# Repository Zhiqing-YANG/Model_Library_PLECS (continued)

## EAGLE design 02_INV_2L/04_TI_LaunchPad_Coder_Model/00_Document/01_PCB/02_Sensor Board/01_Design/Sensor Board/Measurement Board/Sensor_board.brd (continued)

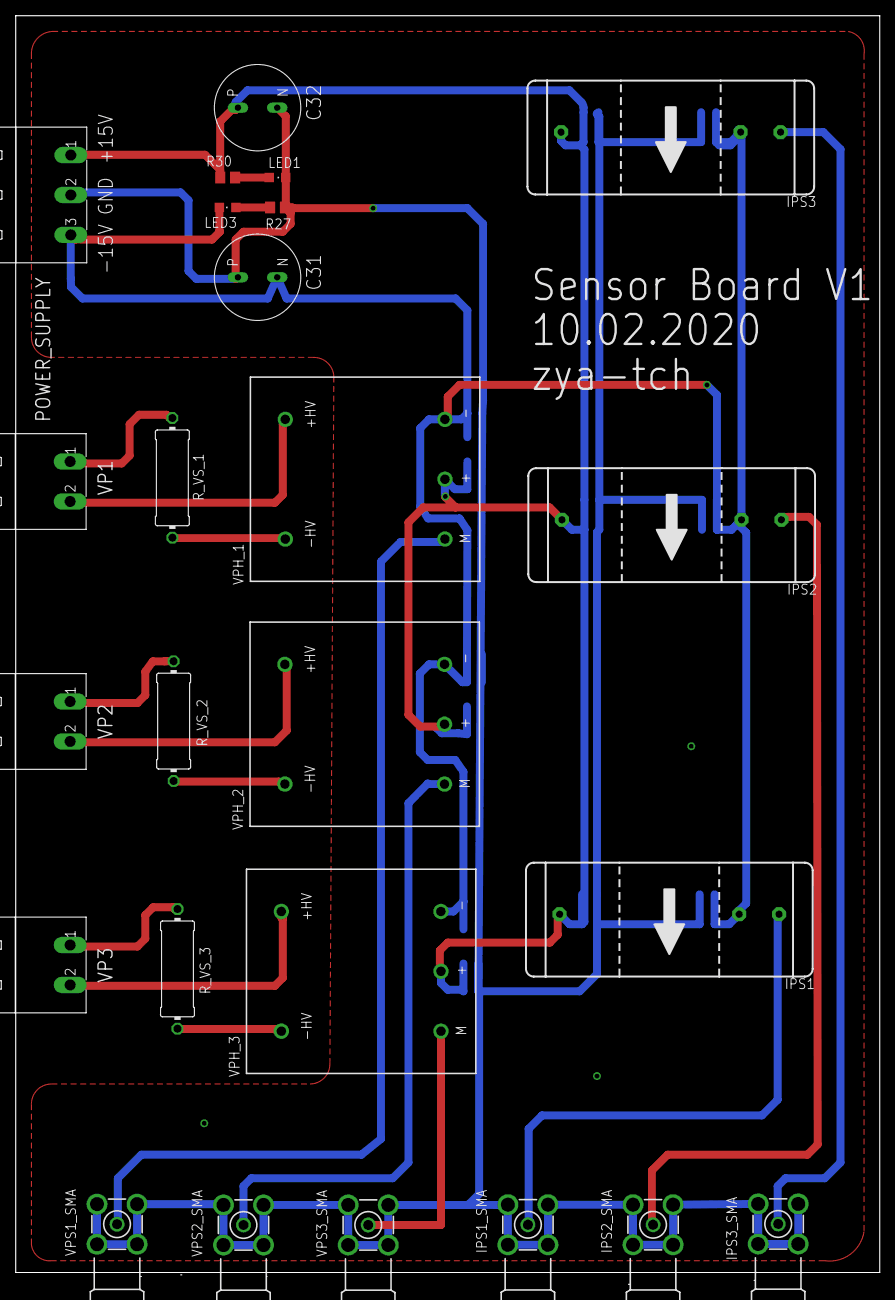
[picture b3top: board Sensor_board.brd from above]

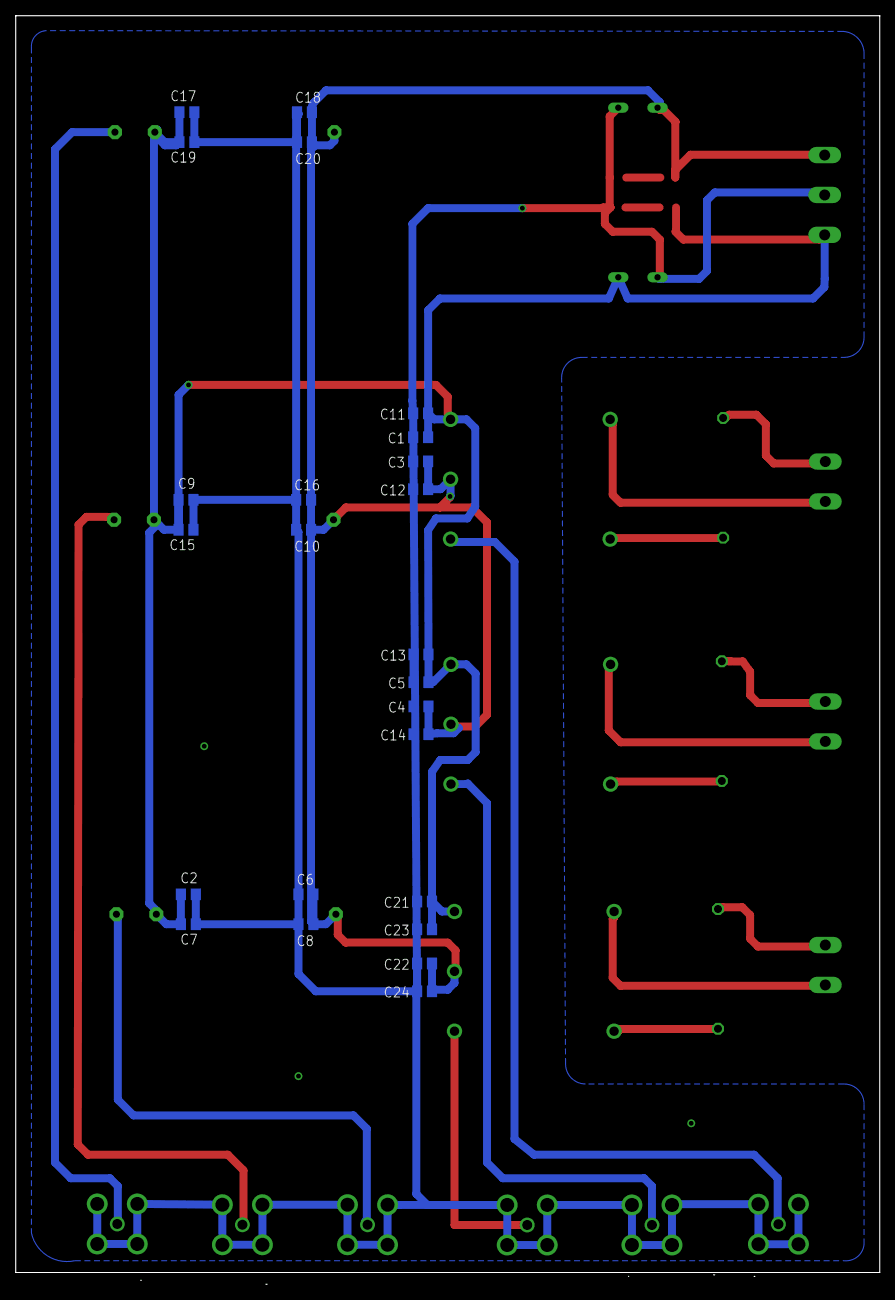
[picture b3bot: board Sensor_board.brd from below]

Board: 2 copper layers, 110.0 x 161.5 mm, 49 parts (24 on the bottom side), 20 nets.

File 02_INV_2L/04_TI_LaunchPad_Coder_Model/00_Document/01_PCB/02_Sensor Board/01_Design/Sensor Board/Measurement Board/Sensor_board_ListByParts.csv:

"Part","Value","Attributes","Package","Description","Part Num"
"C1","1u","","C0805","CAPACITOR, European symbol","*"
"C2","1u","","C0805","CAPACITOR, European symbol","*"
"C3","1u","","C0805","CAPACITOR, European symbol","*"
"C4","1u","","C0805","CAPACITOR, European symbol","*"
"C5","1u","","C0805","CAPACITOR, European symbol","*"
"C6","1u","","C0805","CAPACITOR, European symbol","*"
"C7","100n","","C0805","CAPACITOR, European symbol","*"
"C8","100n","","C0805","CAPACITOR, European symbol","*"
"C9","1u","","C0805","CAPACITOR, European symbol","*"
"C10","1u","","C0805","CAPACITOR, European symbol","*"
"C11","100n","","C0805","CAPACITOR, European symbol","*"
"C12","100n","","C0805","CAPACITOR, European symbol","*"
"C13","100n","","C0805","CAPACITOR, European symbol","*"
"C14","100n","","C0805","CAPACITOR, European symbol","*"
"C15","100n","","C0805","CAPACITOR, European symbol","*"
"C16","100n","","C0805","CAPACITOR, European symbol","*"
"C17","1u","","C0805","CAPACITOR, European symbol","*"
"C18","1u","","C0805","CAPACITOR, European symbol","*"
"C19","100n","","C0805","CAPACITOR, European symbol","*"
"C20","100n","","C0805","CAPACITOR, European symbol","*"
"C21","1u","","C0805","CAPACITOR, European symbol","*"
"C22","1u","","C0805","CAPACITOR, European symbol","*"
"C23","100n","","C0805","CAPACITOR, European symbol","*"
"C24","100n","","C0805","CAPACITOR, European symbol","*"
"C31","ELE_C_470UF_PAN","","ELEK_C_470UF_PAN","","*"
"C32","ELE_C_470UF_PAN","","ELEK_C_470UF_PAN","","*"
"IPS1","LA-25-P","","LA25P","Current Transducer LA 100P","*"
"IPS1_SMA","BU-SMA-H","","BU-SMA-H","FEMALE SMA CONNECTOR","*"
"IPS2","LA-25-P","","LA25P","Current Transducer LA 100P","*"
"IPS2_SMA","BU-SMA-H","","BU-SMA-H","FEMALE SMA CONNECTOR","*"
"IPS3","LA-25-P","","LA25P","Current Transducer LA 100P","*"
"IPS3_SMA","BU-SMA-H","","BU-SMA-H","FEMALE SMA CONNECTOR","*"
"LED1","","","CHIPLED_0805","LED","*"
"LED3","","","CHIPLED_0805","LED","*"
"POWER_SUPPLY","MSTBA3","","MSTBA3","PHOENIX","1757255"
"R27","2k","","R0805","RESISTOR, European symbol","*"
"R30","2k","","R0805","RESISTOR, European symbol","*"
"R_VS_1","21.1k","","0414/15","RESISTOR, European symbol","*"
"R_VS_2","21.1k","","0414/15","RESISTOR, European symbol","*"
"R_VS_3","21.1k","","0414/15","RESISTOR, European symbol","*"
"VP1","MSTBA2","","MSTBA2","PHOENIX","1757242"
"VP2","MSTBA2","","MSTBA2","PHOENIX","1757242"
"VP3","MSTBA2","","MSTBA2","PHOENIX","1757242"
"VPH_1","LV_25-P","","XDCR_LV25-P","Transducer Voltage Close Loop 10ma - Lv 25-p","*"
"VPH_2","LV_25-P","","XDCR_LV25-P","Transducer Voltage Close Loop 10ma - Lv 25-p","*"
"VPH_3","LV_25-P","","XDCR_LV25-P","Transducer Voltage Close Loop 10ma - Lv 25-p","*"
"VPS1_SMA","BU-SMA-H","","BU-SMA-H","FEMALE SMA CONNECTOR","*"
"VPS2_SMA","BU-SMA-H","","BU-SMA-H","FEMALE SMA CONNECTOR","*"
"VPS3_SMA","BU-SMA-H","","BU-SMA-H","FEMALE SMA CONNECTOR","*"

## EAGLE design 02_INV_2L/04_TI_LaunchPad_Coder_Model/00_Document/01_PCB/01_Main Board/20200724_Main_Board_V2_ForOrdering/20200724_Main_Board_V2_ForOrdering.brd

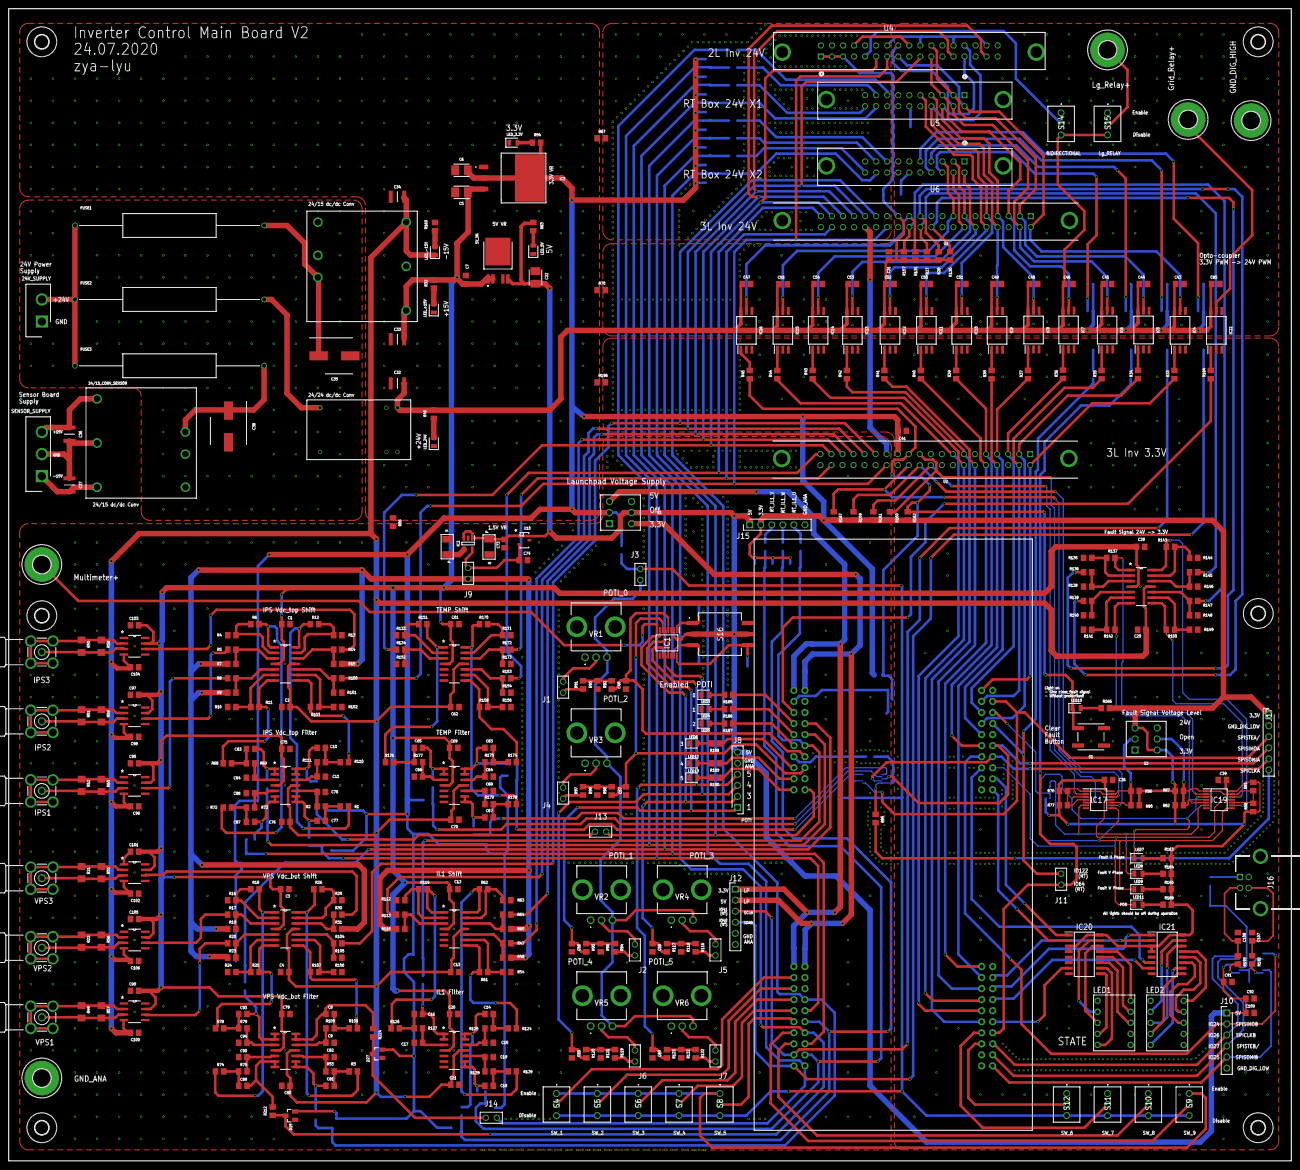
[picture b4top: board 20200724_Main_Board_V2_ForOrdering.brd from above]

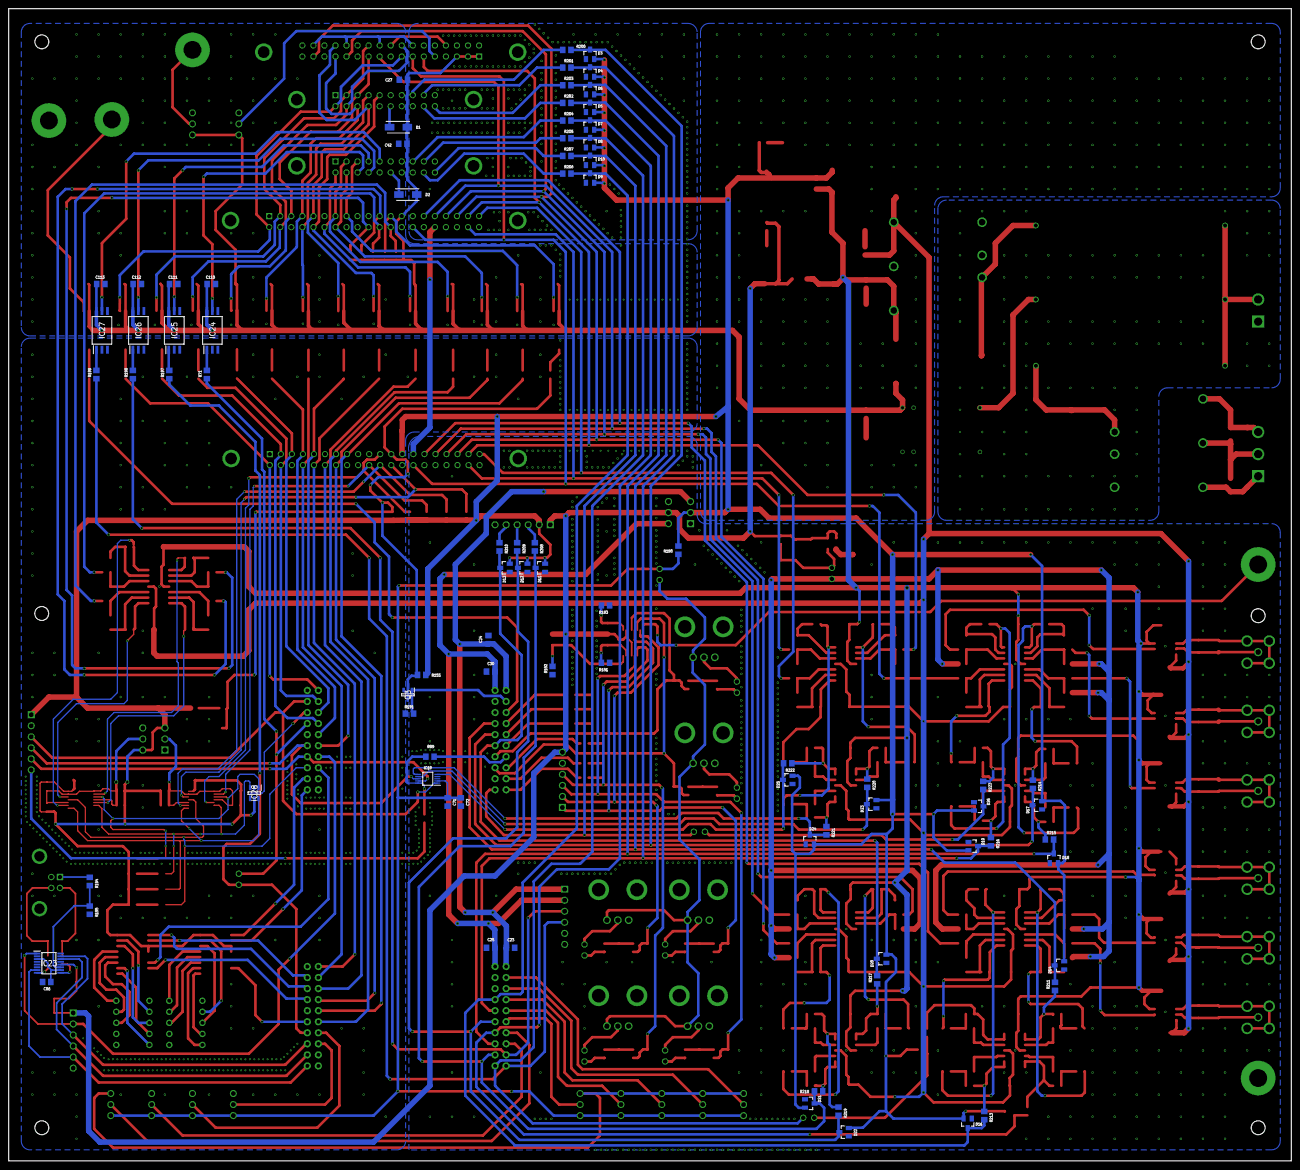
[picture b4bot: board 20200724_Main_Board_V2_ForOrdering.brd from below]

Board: 2 copper layers, 295.0 x 265.0 mm, 498 parts (82 on the bottom side), 344 nets.

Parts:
5V_VR: TLS850B0TEV50ATMA1; BTS6143D
24/15_CONV, 24/15_CONV_SENSOR: CUI_24V_15V_DC/DC_CONV; CUI_24V/15V_DCDC_CONV
24/24_CONV: TRACO_24V_24V_DC/DC_CONV; TRACO_24V/24V_DCDC_CONV
24V_SUPPLY: 1757242; SHDR2W120P0X508_1X2_1208X1200X
C1, C2, C3, C4, C12, C13, C20, C21, C23, C24, C25, C26, C27, C28, C29, C30, C31, C39, C40, C41, C42, C43, C44, C45, C46, C47, C48, C49, C50, C51, C52, C53, C54, C55, C56, C57, C58, C59, C60, C61, C62, C69, C70, C71, C75, C76, C79, C80, C85, C86, C91, C95, C96, C97, C98, C99, C100, C101, C102, C103, C104, C105, C106, C109, C110, C111, C112, C113: 0.1u; C0805
C5, C6, C22: TPSB106K025T1800; DIONM3528X210N
C7: 100n; C0805
C8, C10, C14, C16, C18, C63, C65, C67, C77, C81, C83, C87, C89, C93: 2n; C0805
C9, C11, C15, C17, C19, C64, C66, C68, C78, C82, C84, C88, C90, C94: 1n; C0805
C32, C33, C34, C36, C37: 10uF Ceramic; CAPC3225X230N
C35, C38: 100uF 50V EEV107M050S9MAA; CAPAE830X1050N
C72, C73, C74: 1u; C0805
C92: 4.7u; C0805
C107, C108: 47p; C0805
D1, D2: RS1A-E3_5AT; DIOM5127X229N
D3, D4, D5, D6, D7, D8, D9, D10, D11, D12, D13, D14, D15, D16, D17, D18, D19, D20, D21, D22, D23, D24, D25, D26, D27: BAS40-04; SOT23
FUSE1, FUSE2, FUSE3: 0213001.MXP; RESAD4350W70L2150D550
H1, H2, H3, H4, H10, H11: MOUNT-HOLE3.2; 3,2
H5, H6, H7, H8, H9: MOUNT-PAD-ROUND4.1; 4,1-PAD
IC1: ADG708BRUZ; SOP65P640X120-16N
IC2: LP3992IMFX-1.5_NOPB; SOT95P280X145-5N
IC3: LM1086ISX-3.3_NOPB; KTT0003B
IC4, IC5, IC6, IC7, IC8, IC9, IC10, IC11, IC12, IC13, IC14, IC15, IC16, IC22, IC24, IC25, IC26, IC27: FOD8480; SOIC127P970X378-6N
IC17, IC19: 74CBTLV3125PW-Q10J; SOP65P640X110-14N
IC18: ADC124S101CIMM_NOPB; SOP50P490X110-10N
IC20, IC21: CD4511BNSR; SOIC127P780X200-16N
IC23: FT220XS-R; SOP64P599X175-16N
IC28: SN74LVC1G11DBVR; SOT95P280X145-6N
IPS1, IPS2, IPS3: BU-SMA-H
J1, J2, J3, J4, J5, J6, J7, J9, J11, J13, J14: M20-9730245; M209730245
J8, J10, J12, J15, J17: M20-9990645; HDRV6W64P0X254_1X6_1524X254X86
J16: 61729-0021BLF; 617290021BLF
LED1, LED2: LA-401VN; LA-401
LED3, LED4, LED5, LED6, LED7, LED8, LED9, LED10, LED11, LED12, LED13: APT2012LSECK_J3-PRV; LEDC2012X75N
LED_3.3V, LED_5V, LED_24V: Green LED APT2012LZGCK; LEDC2012X85N
LED_+15V: Green LED APT2012LZGCK; LEDC2012X85N
LED_-15V: Green LED APT2012LZGCK; LEDC2012X85N
Q3: BSS138BK-215; SOT95P230X110-3N
R1, R2, R3, R53, R68, R69, R72, R73, R74, R75, R78, R79, R108, R109, R110, R111, R124, R125, R126, R127, R128, R129, R174, R175, R176, R177, R178, R179: 2.81k; R0805
R4, R5, R8, R10, R13, R14, R16, R17, R20, R24, R29, R30, R47, R54, R63, R64, R100, R102, R104, R106, R112, R113, R133, R134, R153, R156, R171, R172: 100k; R0805
R6, R7, R9, R11, R12, R15: 26.1k; R0805
R18, R19, R23, R25, R26, R31: 24.6k; R0805
R21, R22, R49, R55, R56, R57: 424; R1206
R27, R28, R92, R130, R131, R157, R159, R160, R161, R162, R167, R181, R182, R183, R191: 1k; R0805
R32, R169: 2k; R0805
R33, R34, R35, R36, R37, R38, R39, R40, R41, R42, R43, R44, R45, R71, R184, R197, R198, R199: 250; R0805
R46: 4k; R0805
R48, R61, R62, R65, R114, R115: 15k; R0805
R50, R51, R52, R58, R59, R60: 500; R1206
R66, R67, R70, R85, R89, R180, R196: 0; R0805
R76, R77, R80, R81, R82, R86, R87, R88, R91, R93, R94, R95, R96, R97, R98, R99, R116, R117, R118, R119, R120, R121, R122, R123, R132, R155, R195: 10k; R0805
R83: 460; R0805
R84: 100; R0805
R101, R103, R105, R107, R151, R152, R154, R158, R170, R173: 30k; R0805
R135, R136, R139, R141, R144, R145, R147, R149: 24k; R0805
R137, R138, R140, R142, R143, R146, R148, R150: 3.3k; R0805
R163, R164, R165, R166, R168, R185, R186, R187, R188, R189, R190: 120; R0805
R192, R193: 27; R0805
R194: 4.7k; R0805
R200, R201, R202, R203, R204, R205, R206, R207, R208, R209, R210, R211, R212, R213, R214, R215, R216, R217, R218, R219, R220, R221, R222, R223, R224: 6.8k; R0805
S1: EVP-BF6C1A000; EVPBF6C1A000
S2, S3: 200MDP1T2B1M2QEH
S4, S5, S6, S7, S8, S9, S10, S11, S12, S14, S15: 200MSP1T1B1M2QEH
S16: A6RS-162RS-P; A6RS162RSP
SENSOR_SUPPLY: 1757255; SHDR3W120P0X508_1X3_1716X1200X
U1, U2: 5499206-9; TYCO_5499206-9
U4: 5499206-8; TYCO_5499206-8
U5, U6: 5499206-4; TYCO_5499206-4
U7, U13: TL084/SO_OPONLINE; TL084/SO_OP_LIB
U10: ISL21080DIH312Z-TK; SOT23-3
U$1, U$2, U$3, U$4, U$6, U$8, U$15: TL084/SO_OPONLINE; TL084/SO_OP_LIB
U$9, U$10: TANTALUM_C_1UF_KEMTANTALUM_C_1UF_KEM; TANTALUM_C_1UF_KEM
U$13: LAUNCHPAD; LAUNCHPAD28379
U$24, U$27, U$28, U$29, U$30, U$31: AD629_DIFFAONLINE; AD629_DIFFA_LIB
VPS1, VPS2, VPS3: BU-SMA-H
VR1, VR2, VR3, VR4, VR5, VR6: PTV09A-4020F-B202; PTV09A4020FB503

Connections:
+1.5V_LP: J9.1, R7.1, R9.1, R15.2, R19.1, R23.1, R31.2, R48.2, R65.2, R115.1
+3.3V_DSP: C23.1, C24.1, J12.1, S2.3, U$13.P$1, U$13.P$41
+3.3V_LM: C6.1, C26.1, C39.1, C41.1, D3.2, D4.2, D5.2, D6.2, D7.2, D8.2, D9.2, D10.2, D11.2, D12.2, D13.2, D14.2, D15.2, D16.2, D17.2, D18.2, D19.2, D20.2, D21.2, D22.2, D23.2, D24.2, D25.2, D26.2, D27.2, IC3.2, IC3.TAB, IC17.14, IC19.14, IC20.3, IC20.4, IC20.16, IC21.3, IC21.4, IC21.16, IC28.5, J15.2, J17.1, R76.1, R77.1, R80.2, R81.2, R82.2, R84.2, R86.1, R87.2, R88.2, R155.1, R159.2, R160.2, R161.2, R162.2, R163.2, R164.2, R165.2, R166.2, R167.2, R168.2, R180.1, S2.2, S3.3, S3.4, U2.25
+3.3V_MOS: C71.1, C72.1, IC18.2, J3.2, R180.2, S4.3, S5.3, S6.3, S7.3, S8.3, S9.3, S10.3, S11.3, S12.3
+5V_DSP: C25.1, C30.1, J12.2, S2.4, U$13.P$21, U$13.P$61
+5V_TLS: 5V_VR.5, C22.1, C73.1, C91.1, C92.1, C109.1, IC1.2, IC1.13, IC2.1, IC2.3, IC23.12, J8.6, J10.1, J15.1, R83.2, S2.5, S16.C1, S16.C2, U10.1, U$9.P
+15V_POWER: 5V_VR.1, 5V_VR.2, 24/15_CONV.P$3, C1.2, C3.2, C5.1, C7.2, C12.2, C20.1, C28.2, C33.2, C61.2, C69.1, C75.1, C79.1, C95.2, C97.2, C99.2, C101.2, C103.2, C105.2, IC3.3, R32.2, U7.4, U13.4, U$1.4, U$2.4, U$3.4, U$4.4, U$6.4, U$8.4, U$15.4, U$24.7, U$27.7, U$28.7, U$29.7, U$30.7, U$31.7
+15V_SENSOR: 24/15_CONV_SENSOR.P$3, C36.2, SENSOR_SUPPLY.3
+24V_POWER: 24/24_CONV.P$9, C27.1, C31.1, C32.2, C42.1, C43.1, C44.1, C45.1, C46.1, C47.1, C48.1, C49.1, C50.1, C51.1, C52.1, C53.1, C54.1, C55.1, C85.1, C110.1, C111.1, C112.1, C113.1, D1.2, D2.2, IC4.6, IC5.6, IC6.6, IC7.6, IC8.6, IC9.6, IC10.6, IC11.6, IC12.6, IC13.6, IC14.6, IC15.6, IC16.6, IC22.6, IC24.6, IC25.6, IC26.6, IC27.6, R27.2, R28.2, R46.2, R130.2, R131.2, R157.2, S14.3, S15.3, U1.25, U4.1, U4.3, U4.5
+24V_TBA: 24V_SUPPLY.2, FUSE1.1, FUSE2.1, FUSE3.1
-15V_POWER: 24/15_CONV.P$5, C2.2, C4.2, C13.2, C21.1, C29.2, C34.1, C62.2, C70.1, C76.1, C80.1, C96.2, C98.2, C100.2, C102.2, C104.2, C106.2, LED_-15V.1, U7.11, U13.11, U$1.11, U$2.11, U$3.11, U$4.11, U$6.11, U$8.11, U$15.11, U$24.4, U$27.4, U$28.4, U$29.4, U$30.4, U$31.4
-15V_SENSOR: 24/15_CONV_SENSOR.P$5, C37.1, SENSOR_SUPPLY.1
ACC_IREF: C40.1, IC1.4, R92.1, U$13.P$27
ACC_KP: C56.1, IC1.5, J8.1, R95.1
ADC/DAC1: D10.3, J13.1, R207.2, U$13.P$30
ADC/DAC2: D8.3, J14.1, R205.2, U$13.P$70
BIDIRECTIONAL: S14.2, U4.9
CLEAR_FAULT_3.3V: LED10.1, Q3.3, R45.1, R155.2, R162.1, S1.A1, U2.23
CLEAR_FAULT_24V: IC16.5, R131.1, U1.23
EN_3.3V: IC17.1, IC17.4, IC17.10, IC17.13, R76.2, R77.2, R80.1, R86.2, S3.2
EN_24V: IC19.1, IC19.4, IC19.10, IC19.13, R81.1, R82.1, R87.1, R88.1, S3.5
EXTRA_KNOB: C60.1, IC1.11, J8.4, R123.1
FAULT_3.3V: IC28.4, U$13.P$18
FAULT_U_3.3V: IC17.3, IC19.3, IC28.1, LED7.1
FAULT_U_24V: R130.1, R136.1, U1.20
FAULT_U_INV3.3: IC17.2, R161.1, U2.20
FAULT_U_INV24: IC19.2, R137.2, U$8.1
FAULT_V_3.3V: IC17.6, IC19.6, IC28.3, LED8.1
FAULT_V_24V: R28.1, R139.1, U1.21
FAULT_V_INV3.3: IC17.5, R160.1, U2.21
FAULT_V_INV24: IC19.5, R142.2, U$8.7
FAULT_W_3.3V: IC17.8, IC19.8, IC28.6, LED9.1
FAULT_W_24V: R27.1, R145.2, U1.22
FAULT_W_INV3.3: IC17.9, R159.1, U2.22
FAULT_W_INV24: IC19.9, R143.1, U$8.14
GND_ANA: C1.1, C2.1, C3.1, C4.1, C9.2, C11.2, C12.1, C13.1, C15.2, C17.2, C19.2, C20.2, C21.2, C23.2, C24.2, C25.2, C30.2, C40.2, C56.2, C57.2, C58.2, C59.2, C60.2, C61.1, C62.1, C64.2, C66.2, C68.2, C69.2, C70.2, C71.2, C72.2, C73.2, C74.2, C75.2, C76.2, C78.2, C79.2, C80.2, C82.2, C84.2, C88.2, C90.2, C94.2, C95.1, C96.1, C97.1, C98.1, C99.1, C100.1, C101.1, C102.1, C103.1, C104.1, C105.1, C106.1, D3.1, D4.1, D5.1, D6.1, D7.1, D8.1, D9.1, D10.1, D11.1, D12.1, D13.1, D14.1, D15.1, D16.1, D17.1, D18.1, D19.1, D20.1, D21.1, D22.1, D23.1, D24.1, D25.1, D26.1, D27.1, H9.B4,1, IC1.3, IC1.14, IC2.2, IC18.3, IC18.4, J8.5, J12.5, J12.6, J15.6, LED3.1, LED4.1, LED5.1, LED6.1, LED12.1, LED13.1, R4.1, R10.1, R13.2, R16.1, R24.1, R29.2, R54.2, R63.2, R66.2, R67.2, R93.1, R96.1, R99.1, R101.2, R102.2, R105.2, R106.2, R112.1, R118.1, R121.1, R132.1, R133.1, R152.1, R154.2, R156.2, R171.2, R173.2, R181.1, R182.1, R183.1, U1.27, U1.30, U1.32, U1.34, U1.36, U2.27, U2.30, U2.32, U2.34, U2.36, U4.2, U4.4, U4.6, U4.12, U4.14, U4.20, U4.26, U4.32, U5.16, U5.19, U6.16, U6.19, U10.3, U$9.N, U$10.N, U$13.P$22, U$13.P$62, U$24.1, U$24.5, U$27.1, U$27.5, U$28.1, U$28.5, U$29.1, U$29.5, U$30.1, U$30.5, U$31.1, U$31.5, VR1.1, VR2.1, VR3.1, VR4.1, VR5.1, VR6.1
GND_DIG_HIGH: C27.2, C31.2, C42.2, C43.2, C44.2, C45.2, C46.2, C47.2, C48.2, C49.2, C50.2, C51.2, C52.2, C53.2, C54.2, C55.2, C85.2, C110.2, C111.2, C112.2, C113.2, H5.B4,1, IC4.4, IC5.4, IC6.4, IC7.4, IC8.4, IC9.4, IC10.4, IC11.4, IC12.4, IC13.4, IC14.4, IC15.4, IC16.4, IC22.4, IC24.4, IC25.4, IC26.4, IC27.4, R70.2, S14.1, S15.1, U1.1, U1.6, U1.11, U1.16, U1.26, U4.8, U4.18, U4.24, U4.30, U5.14, U6.14
GND_DIG_LOW: C26.2, C28.1, C29.1, C39.2, C41.2, C86.2, C91.2, C92.2, C107.2, C108.2, C109.2, IC4.3, IC5.3, IC6.3, IC7.3, IC8.3, IC9.3, IC10.3, IC11.3, IC12.3, IC13.3, IC14.3, IC15.3, IC16.3, IC17.7, IC19.7, IC20.5, IC20.6, IC20.8, IC21.5, IC21.8, IC22.3, IC23.5, IC23.13, IC24.3, IC25.3, IC26.3, IC27.3, IC28.2, J10.6, J16.4, J17.2, LED1.1, LED1.6, LED1.7, LED2.1, LED2.6, LED2.7, Q3.2, R135.1, R138.1, R140.1, R141.1, R144.2, R146.2, R148.2, R149.2, R191.1, R195.2, R196.2, S1.B1, S3.1, S3.6, S4.1, S5.1, S6.1, S7.1, S8.1, S9.1, S10.1, S11.1, S12.1, U2.1, U2.6, U2.11, U2.16, U2.26, U$13.P$20, U$13.P$60
GND_POWER: 5V_VR.3, 24/15_CONV.P$4, 24/24_CONV.P$10, C5.2, C6.2, C7.1, C22.2, C32.1, C33.1, C34.2, IC3.1, LED_3.3V.1, LED_5V.1, LED_24V.1, LED_+15V.1, R66.1, R67.1, R70.1, R169.2, R196.1
GND_SENSOR: 24/15_CONV_SENSOR.P$4, C36.1, C37.2, SENSOR_SUPPLY.2
GND_TBA: 24/15_CONV.P$1, 24/15_CONV_SENSOR.P$1, 24/24_CONV.P$1, 24V_SUPPLY.1, C35.2, C38.2
IL1_U_10V: R113.1, U1.31, U2.31, U4.19
IL1_U_FILTER: C17.1, R127.2, U13.3
IL1_U_OUT: D13.3, D20.3, R210.2, R217.2, U$13.P$26
IL1_U_PROTECT: C16.1, R217.1, U13.1, U13.2
IL1_U_SH: R114.2, R126.1, U$15.1
IL1_V_10V: R64.2, U1.33, U2.33, U4.25
IL1_V_FILTER: C19.1, R129.2, U13.10
IL1_V_OUT: D11.3, D21.3, R208.2, R218.2, U$13.P$69
IL1_V_PROTECT: C18.1, R218.1, U13.8, U13.9
IL1_V_SH: R62.1, R128.1, U$15.14
IL1_W_10V: R47.2, U1.35, U2.35, U4.31
IL1_W_FILTER: C15.1, R125.2, U13.12
IL1_W_OUT: D12.3, D22.3, R209.2, R219.2, U$13.P$66
IL1_W_PROTECT: C14.1, R219.1, U13.13, U13.14
IL1_W_SH: R61.1, R124.1, U$15.8
IPS1_AD: R8.1, U$24.6
IPS1_FILTER: C84.1, R69.2, U$4.3
IPS1_N: IPS1.2, IPS1.3, IPS1.4, IPS1.5, R52.1, R60.1, U$24.2
IPS1_OUT: D3.3, D17.3, R200.2, R214.2, U$13.P$25
IPS1_P: IPS1.1, R52.2, R60.2, U$24.3
IPS1_PROTECT: C83.1, R214.1, U$4.1, U$4.2
IPS1_SH: R11.2, R68.1, U$1.7
IPS2_AD: R5.1, U$27.6
IPS2_FILTER: C88.1, R73.2, U$4.5
IPS2_N: IPS2.2, IPS2.3, IPS2.4, IPS2.5, R51.1, R59.1, U$27.2
IPS2_OUT: D5.3, D18.3, R202.2, R215.2, U$13.P$68
IPS2_P: IPS2.1, R51.2, R59.2, U$27.3
IPS2_PROTECT: C87.1, R215.1, U$4.6, U$4.7
IPS2_SH: R6.2, R72.1, U$1.1
IPS3_AD: R14.2, U$30.6
IPS3_FILTER: C78.1, R2.2, U$4.10
IPS3_N: IPS3.2, IPS3.3, IPS3.4, IPS3.5, R50.1, R58.1, U$30.2
IPS3_OUT: D4.3, D19.3, R201.2, R216.2, U$13.P$65
IPS3_P: IPS3.1, R50.2, R58.2, U$30.3
IPS3_PROTECT: C77.1, R216.1, U$4.8, U$4.9
IPS3_SH: R1.1, R12.1, U$1.14
MBC_KPC: C58.1, IC1.7, J8.2, R117.1
MULTIMETER+: H8.B4,1, IC1.8
MUX_A0: IC1.1, R183.2, S16.1
MUX_A1: IC1.16, R182.2, S16.2
MUX_A2: IC1.15, R181.2, S16.4
unnamed: LED_+15V.2, R32.1
unnamed: R147.1, R148.1, U$8.10
unnamed: R4.2, R6.1, U$1.2
unnamed: R5.2, R7.2, U$1.3
unnamed: R16.2, R18.1, U$3.2
unnamed: R10.2, R11.1, U$1.6
unnamed: R8.2, R9.2, U$1.5
unnamed: R17.2, R19.2, U$3.3
unnamed: C77.2, R1.2, R2.1
unnamed: C81.2, R3.2, R53.1
unnamed: C83.2, R68.2, R69.1
unnamed: LED_5V.2, R83.1
unnamed: IC4.1, R33.2
unnamed: LED_3.3V.2, R84.1
unnamed: C87.2, R72.2, R73.1
unnamed: R20.2, R23.2, U$3.5
unnamed: C89.2, R74.2, R75.1
unnamed: IC5.1, R34.2
unnamed: C93.2, R78.2, R79.1
unnamed: R12.2, R13.1, U$1.13
unnamed: R14.1, R15.1, U$1.12
unnamed: R24.2, R25.1, U$3.6
unnamed: R26.2, R29.1, U$3.13
unnamed: R30.1, R31.1, U$3.12
unnamed: IC6.1, R35.2
unnamed: IC7.1, R36.2
unnamed: IC8.1, R37.2
unnamed: IC9.1, R38.2
unnamed: IC10.1, R39.2
unnamed: IC11.1, R40.2
unnamed: IC12.1, R41.2
unnamed: IC13.1, R42.2
unnamed: IC14.1, R43.2
unnamed: IC15.1, R44.2
unnamed: IC16.1, R45.2
unnamed: LED_24V.2, R46.1
unnamed: 24/15_CONV.P$2, C35.1, FUSE1.2
unnamed: 24/24_CONV.P$16, FUSE2.2
unnamed: 24/15_CONV_SENSOR.P$2, C38.1, FUSE3.2
unnamed: R47.1, R48.1, U$15.10
unnamed: R54.1, R61.2, U$15.9
unnamed: J1.2, VR1.2
unnamed: R62.2, R63.1, U$15.13
unnamed: R64.1, R65.1, U$15.12
unnamed: J2.2, VR2.2
unnamed: J4.2, VR3.2
unnamed: R200.1, U5.15
unnamed: Q3.1, R191.2, U$13.P$2
unnamed: R190.1, U$13.P$10
unnamed: R201.1, U5.17
unnamed: C86.1, IC23.3, IC23.10
unnamed: J5.2, VR4.2
unnamed: J6.2, VR5.2
unnamed: R100.1, R101.1, U$1.10
unnamed: R104.1, R105.1, U$3.10
unnamed: R106.1, R107.2, U$3.9
unnamed: C8.2, R108.2, R109.1
unnamed: R102.1, R103.2, U$1.9
unnamed: C10.2, R110.2, R111.1
unnamed: R112.2, R114.1, U$15.2
unnamed: R113.2, R115.2, U$15.3
unnamed: J7.2, VR6.2
unnamed: J1.1, R91.2
unnamed: R91.1, R92.2, R93.2
unnamed: D2.1, U6.12
unnamed: C14.2, R124.2, R125.1
unnamed: C16.2, R126.2, R127.1
unnamed: C18.2, R128.2, R129.1
unnamed: J3.1, VR1.3, VR2.3, VR3.3, VR4.3, VR5.3, VR6.3
unnamed: R135.2, R137.1, U$8.2
unnamed: R136.2, R138.2, U$8.3
unnamed: R139.2, R140.2, U$8.5
unnamed: R141.2, R142.1, U$8.6
unnamed: R143.2, R144.1, U$8.13
unnamed: R145.1, R146.1, U$8.12
unnamed: IC2.4, U$10.P
unnamed: R149.1, R150.2, U$8.9
unnamed: J2.1, R94.2
unnamed: R94.1, R95.2, R96.2
unnamed: D1.1, U5.12
unnamed: J4.1, R97.2
unnamed: LED7.2, R163.1
unnamed: LED8.2, R164.1
unnamed: LED9.2, R165.1
unnamed: LED10.2, R166.1
unnamed: LED11.2, R168.1
unnamed: LED_-15V.2, R169.1
unnamed: R97.1, R98.2, R99.2
unnamed: C74.1, IC2.5, J9.2, U10.2
unnamed: J5.1, R116.2
unnamed: R116.1, R117.2, R118.2
unnamed: R133.2, R151.1, U$2.2
unnamed: R134.2, R152.2, U$2.3
unnamed: R153.1, R154.1, U$2.10
unnamed: R119.1, R120.2, R121.2
unnamed: J6.1, R119.2
unnamed: R156.1, R158.2, U$2.9
unnamed: J7.1, R122.2
unnamed: R122.1, R123.2, R132.2
unnamed: R170.2, R171.1, U$2.13
unnamed: R172.1, R173.1, U$2.12
unnamed: C63.2, R174.2, R175.1
unnamed: C65.2, R176.2, R177.1
unnamed: C67.2, R178.2, R179.1
unnamed: IC23.11, R194.2, R195.1
unnamed: LED3.2, R185.2
unnamed: LED4.2, R186.2
unnamed: LED5.2, R187.2
unnamed: LED6.2, R188.2
unnamed: IC20.15, LED1.2
unnamed: IC20.14, LED1.3
unnamed: IC20.13, LED1.10
unnamed: IC20.12, LED1.9
unnamed: IC20.11, LED1.8
unnamed: IC20.10, LED1.5
unnamed: IC20.9, LED1.4
unnamed: LED12.2, R189.2
unnamed: IC21.15, LED2.2
unnamed: R203.1, U5.20
unnamed: R202.1, U5.18
unnamed: IC21.14, LED2.3
unnamed: IC21.13, LED2.10
unnamed: IC21.12, LED2.9
unnamed: IC21.11, LED2.8
unnamed: IC21.10, LED2.5
unnamed: IC21.9, LED2.4
unnamed: LED13.2, R190.2
unnamed: IC22.1, R184.2
unnamed: C108.1, J16.2, R193.1
unnamed: R185.1, U$13.P$4
unnamed: R186.1, U$13.P$5
unnamed: R187.1, U$13.P$6
unnamed: IC23.8, R192.2
unnamed: R188.1, U$13.P$8
unnamed: R189.1, U$13.P$9
unnamed: C107.1, J16.3, R192.1
unnamed: IC24.1, R71.2
unnamed: IC25.1, R197.2
unnamed: IC23.9, R193.2
unnamed: IC26.1, R198.2
unnamed: IC27.1, R199.2
unnamed: R204.1, U6.15
unnamed: R206.1, U6.18
unnamed: J16.1, R194.1
unnamed: R205.1, U6.17
unnamed: R207.1, U6.20
unnamed: J15.3, R208.1
unnamed: J15.4, R209.1
unnamed: J15.5, R210.1
unnamed: J17.6, R85.2
unnamed: R89.2, U$13.P$7
PLL_BW: C57.1, IC1.6, R98.1, U$13.P$28
POR_3.3V: IC17.11, IC19.11, LED11.1, U$13.P$13
POR_24V: R147.2, R157.1, U1.24
POR_INV3.3: IC17.12, R167.1, U2.24
POR_INV24: IC19.12, R150.1, U$8.8
PWM_3.3V_U1: R33.1, U2.2, U$13.P$40
PWM_3.3V_U2: R34.1, U2.3, U$13.P$37
PWM_3.3V_U3: R35.1, U2.4, U$13.P$39
PWM_3.3V_U4: R36.1, U2.5, U$13.P$38
PWM_3.3V_V1: R37.1, U2.7, U$13.P$36
PWM_3.3V_V2: R38.1, U2.8, U$13.P$79
PWM_3.3V_V3: R39.1, U2.9, U$13.P$35
PWM_3.3V_V4: R40.1, U2.10, U$13.P$80
PWM_3.3V_W1: R41.1, U2.12, U$13.P$78
PWM_3.3V_W2: R42.1, U2.13, U$13.P$75
PWM_3.3V_W3: R43.1, U2.14, U$13.P$77
PWM_3.3V_W4: R44.1, U2.15, U$13.P$76
PWM_24V_U1: IC4.5, U1.2, U4.15, U5.2
PWM_24V_U2: IC5.5, U1.3, U4.22, U5.3
PWM_24V_U3: IC6.5, U1.4, U4.16, U5.4
PWM_24V_U4: IC7.5, U1.5, U4.21, U5.5
PWM_24V_V1: IC8.5, U1.7, U4.27, U5.6
PWM_24V_V2: IC9.5, U1.8, U5.7
PWM_24V_V3: IC10.5, U1.9, U4.28, U5.8
PWM_24V_V4: IC11.5, U1.10, U5.9
PWM_24V_W1: IC12.5, U1.12, U6.2
PWM_24V_W2: IC13.5, U1.13, U6.3
PWM_24V_W3: IC14.5, U1.14, U6.4
PWM_24V_W4: IC15.5, U1.15, U6.5
RELAY_GRID_3.3V: R184.1, U$13.P$3
RELAY_GRID_24V: H7.B4,1, IC22.5
RELAY_LG_24V: H6.B4,1, S15.2
RT_GPIO_1_3.3V: J11.1, R71.1, U$13.P$17
RT_GPIO_1_24V: IC24.5, U6.6
RT_GPIO_2_3.3V: J11.2, R197.1, U$13.P$54
RT_GPIO_2_24V: IC25.5, U6.7
RT_GPIO_3_3.3V: J12.3, R198.1, U$13.P$49
RT_GPIO_3_24V: IC26.5, U6.8
RT_GPIO_4_3.3V: J12.4, R199.1, U$13.P$50
RT_GPIO_4_24V: IC27.5, U6.9
SPI_A_CLK: IC18.10, R85.1, R89.1
SPI_A_S/S/: IC18.1, J17.3, U$13.P$19
SPI_A_SIMO: IC18.8, J17.4, U$13.P$15
SPI_A_SOMI: IC18.9, J17.5, U$13.P$14
SPI_B_CLK: IC23.15, J10.3, U$13.P$53
SPI_B_S/S/: IC23.14, J10.4, U$13.P$52
SPI_B_SIMO: IC23.1, J10.2, U$13.P$34
SPI_B_SOMI: IC23.7, J10.5, U$13.P$51
STATE_TENS0: IC20.7, U$13.P$55
STATE_TENS1: IC20.1, U$13.P$12
STATE_TENS2: IC20.2, U$13.P$11
STATE_UNITS0: IC21.7, U$13.P$57
STATE_UNITS1: IC21.1, U$13.P$58
STATE_UNITS2: IC21.2, U$13.P$59
STATE_UNITS3: IC21.6, U$13.P$33
TEMP_U_10V: R134.1, U1.37, U2.37, U4.11
TEMP_U_FILTER: C66.1, R177.2, U7.3
TEMP_U_OUT: D23.3, IC18.7, R220.2
TEMP_U_PROTECT: C65.1, R220.1, U7.1, U7.2
TEMP_U_SH: R151.2, R176.1, U$2.1
TEMP_V_10V: R172.2, U1.38, U2.38
TEMP_V_FILTER: C68.1, R179.2, U7.10
TEMP_V_OUT: D24.3, IC18.6, R221.2
TEMP_V_PROTECT: C67.1, R221.1, U7.8, U7.9
TEMP_V_SH: R170.1, R178.1, U$2.14
TEMP_W_10V: R153.2, U1.39, U2.39
TEMP_W_FILTER: C64.1, R175.2, U7.12
TEMP_W_OUT: D25.3, IC18.5, R222.2
TEMP_W_PROTECT: C63.1, R222.1, U7.13, U7.14
TEMP_W_SH: R158.1, R174.1, U$2.8
TS_ACC: S6.2, U$13.P$44
TS_BW: S8.2, U$13.P$46
TS_EXTRA1: S11.2, U$13.P$74
TS_EXTRA2: S12.2, U$13.P$73
TS_GRID: S5.2, U$13.P$43
TS_KP: S7.2, U$13.P$45
TS_KPC: S9.2, U$13.P$47
TS_OLPLL: S4.2, U$13.P$42
TS_VD: S10.2, U$13.P$48
VDC_BOT_10V: R104.2, U1.29, U2.29
VDC_BOT_FILTER: C9.1, R109.2, U$6.12
VDC_BOT_OUT: D27.3, J14.2, R224.2
VDC_BOT_PROTECT: C8.1, R224.1, U$6.13, U$6.14
VDC_BOT_SH: R107.1, R108.1, U$3.8
VDC_TOP_10V: R100.2, U1.28, U2.28, U4.13
VDC_TOP_FILTER: C11.1, R111.2, U$4.12
VDC_TOP_OUT: D26.3, J13.2, R223.2
VDC_TOP_PROTECT: C10.1, R223.1, U$4.13, U$4.14
VDC_TOP_SH: R103.1, R110.1, U$1.8
VDC_VD: C59.1, IC1.12, J8.3, R120.1
VPS1_AD: R20.1, U$28.6
VPS1_FILTER: C94.1, R79.2, U$6.3
VPS1_N: R49.1, R57.1, U$28.2, VPS1.2, VPS1.3, VPS1.4, VPS1.5
VPS1_OUT: D6.3, D14.3, R203.2, R211.2, U$13.P$24
VPS1_P: R49.2, R57.2, U$28.3, VPS1.1
VPS1_PROTECT: C93.1, R211.1, U$6.1, U$6.2
VPS1_SH: R25.2, R78.1, U$3.7
VPS2_AD: R17.1, U$29.6
VPS2_FILTER: C90.1, R75.2, U$6.5
VPS2_N: R22.1, R56.1, U$29.2, VPS2.2, VPS2.3, VPS2.4, VPS2.5
VPS2_OUT: D7.3, D15.3, R204.2, R212.2, U$13.P$67
VPS2_P: R22.2, R56.2, U$29.3, VPS2.1
VPS2_PROTECT: C89.1, R212.1, U$6.6, U$6.7
VPS2_SH: R18.2, R74.1, U$3.1
VPS3_AD: R30.2, U$31.6
VPS3_FILTER: C82.1, R53.2, U$6.10
VPS3_N: R21.1, R55.1, U$31.2, VPS3.2, VPS3.3, VPS3.4, VPS3.5
VPS3_OUT: D9.3, D16.3, R206.2, R213.2, U$13.P$64
VPS3_P: R21.2, R55.2, U$31.3, VPS3.1
VPS3_PROTECT: C81.1, R213.1, U$6.8, U$6.9
VPS3_SH: R3.1, R26.1, U$3.14

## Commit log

2020-09-03 Create try
2020-10-09 add model DAB3
2020-11-02 change version
2020-11-02 Revert "add model DAB3"
    This reverts commit 46ef855fff7f2f3714e867a47d0e48a3b5553452.
2020-11-02 creat DAB3 main folder
2020-11-02 create main folder of 2L-INV model
2020-11-02 add DAB3 SPS
2020-11-06 update model from Huixue
2020-11-25 Add 2L inverter models
2021-01-12 update model with measurement ports
2021-03-25 New Model from Huixue
2021-04-04 update
    update
2021-04-21 update inverter model
2021-04-21 Update Model
    Impedance model
    TI launchpad model
    State-space model
2021-07-17 Explain the Motivation of the folder
2021-07-17 Reorganize folders
2021-07-21 Parameter update after test
2021-07-26 Update SSM
2021-07-27 Update switching model
    1. delate last change, only keep establish
    2. 2*pi*fg -> wg
    3. refine function text
2021-07-27 Update switching models
2021-07-29 Update
    1. swithcing model
    2. state-space model
2021-08-03 Update Simulation Model
2021-08-05 Update Switching Model
    1. Add Ctrl.T_dh
    2. Update Block Name in Switching Model
2021-08-05 Model Update
    1. Update switching model for 1kW system
    2. Update impedance model for 1kW system
2021-08-05 Model Update
    1. Update state-space model
2021-08-05 Model Update
    1. Update TI LaunchPad Model
2021-08-06 Model Update
    1. Update Impedance model plot function
2021-08-07 Model Update
    1. Update Bode plot
    2. Update passivity plot
    3. Update Nyquist plot
    4. Update frequency response
2021-08-07 Model Update
    1. Update auxiliary function for impedance models
2021-08-08 Update Model
    1. Update all switching models
2021-08-08 Update Model
    1. Update impedance model calculation files
2021-08-08 Model Update
2021-08-15 Model Update
    1. Update TI coder model
    2. Update switching model AVC
2021-08-15 Model Update
    1. Update documentation of coder model
2021-08-16 Model Update
    1. Update coder model after experiments
2021-10-12 update 3L model
2021-12-24 Update impedance model derivation
2022-01-03 Update Impedance Model
    1. file name
    2. solve_eig
2022-01-03 Update Impedance model
